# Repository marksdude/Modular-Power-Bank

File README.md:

# Modular-Power-Bank
A power bank with attachable modules
# Disclamer
None of the PCBs have been fully tested so I can't guarantee that they will function correctly.
# Features
- USB PD output up to 45W (may handle 60W)
- 0.91 inch OLED for status monitoring
- Attachable modules
- Repairable design
# Modules
- LED controller - Allows you to control 5V LEDs with Home Assistant

I also plan to make a LiPo charger module that will support charging up to 3S LiPos.

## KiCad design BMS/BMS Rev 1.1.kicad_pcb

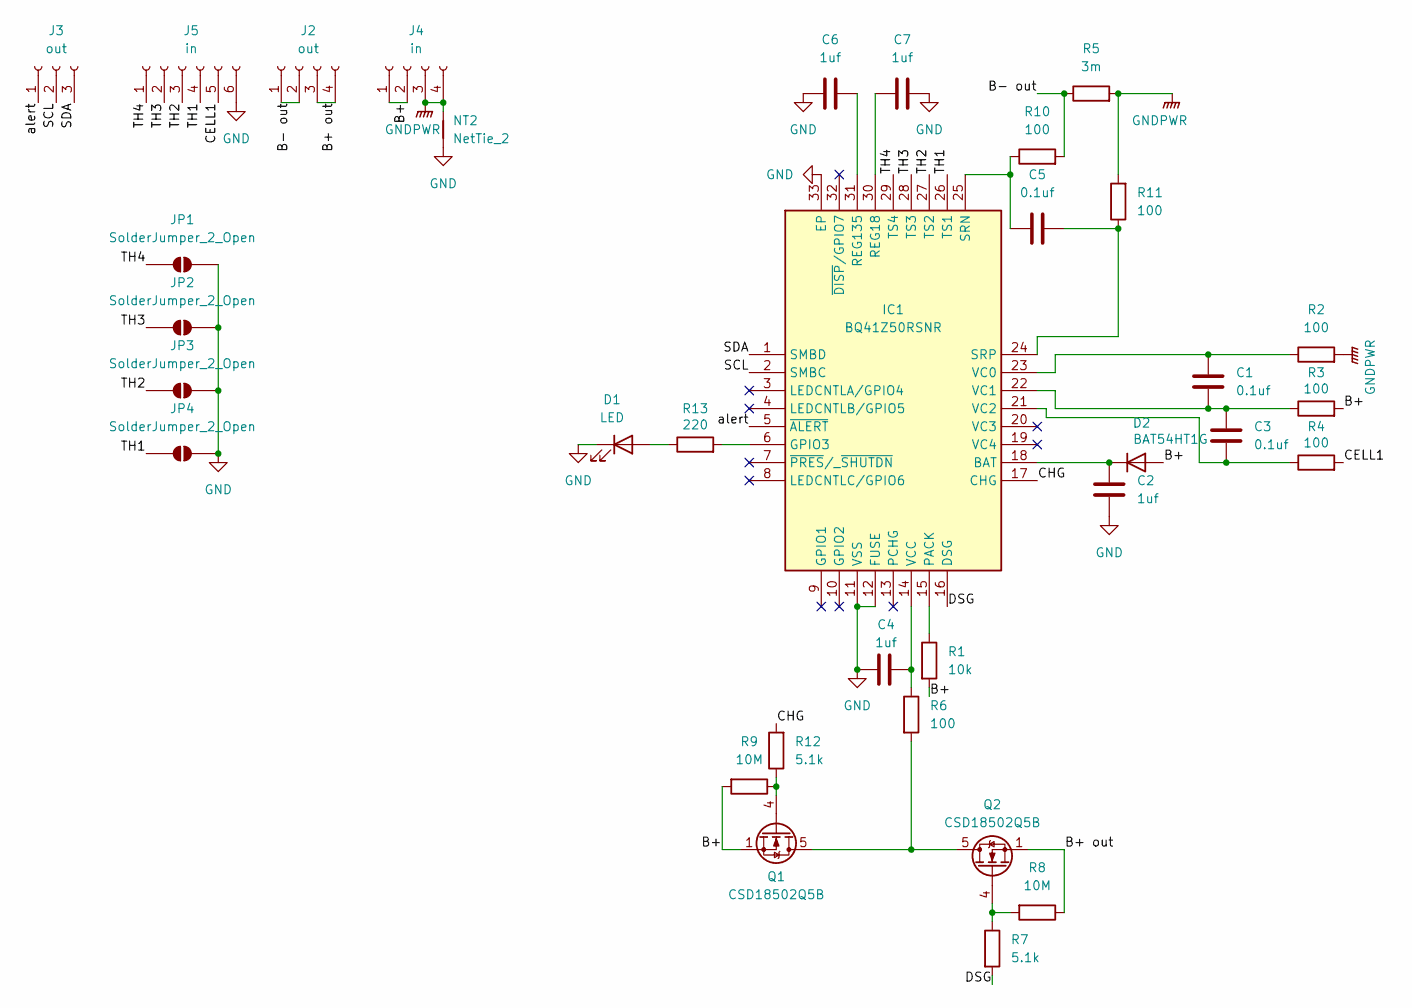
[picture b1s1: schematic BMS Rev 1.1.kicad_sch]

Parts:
C1, C3: 0.1uf; C_0402_1005Metric_Pad0.74x0.62mm_HandSolder
C2, C4, C6, C7: 1uf; C_0402_1005Metric_Pad0.74x0.62mm_HandSolder
C5: 0.1uf; C_0201_0603Metric_Pad0.64x0.40mm_HandSolder
D1: LED; LED_0402_1005Metric_Pad0.77x0.64mm_HandSolder
D2: BAT54HT1G; D_SOD-323_HandSoldering
IC1: BQ41Z50RSNR; QFN40P400X400X80-33N-D; Manufacturer_Part_Number BQ41Z50RSNR
J2: out; JST_VH_S4P-VH_1x04_P3.96mm_Horizontal
J3: out; JST_ZH_B3B-ZR_1x03_P1.50mm_Vertical
J4: in; JST_VH_S4P-VH_1x04_P3.96mm_Horizontal
J5: in; JST_ZH_B6B-ZR_1x06_P1.50mm_Vertical
JP1, JP2, JP3, JP4: SolderJumper_2_Open; SolderJumper-2_P1.3mm_Open_RoundedPad1.0x1.5mm
NT2: NetTie_2; NetTie-2_SMD_Pad0.5mm
Q1, Q2: CSD18502Q5B; TDSON-8-1
R1: 10k; R_0603_1608Metric_Pad0.98x0.95mm_HandSolder
R2, R3, R4, R10, R11: 100; R_0402_1005Metric_Pad0.72x0.64mm_HandSolder
R5: 3m; R_2512_6332Metric_Pad1.40x3.35mm_HandSolder
R6: 100; R_0603_1608Metric_Pad0.98x0.95mm_HandSolder
R7, R12: 5.1k; R_0402_1005Metric_Pad0.72x0.64mm_HandSolder
R8, R9: 10M; R_0402_1005Metric_Pad0.72x0.64mm_HandSolder
R13: 220; R_0402_1005Metric_Pad0.72x0.64mm_HandSolder

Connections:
/B+: D2.2 (A), J4.1, J4.2, Q1.1 (S), Q1.2 (S), Q1.3 (S), R1.2, R3.2, R9.2
/B+ out: J2.3, J2.4, Q2.1 (S), Q2.2 (S), Q2.3 (S), R8.1
/B- out: J2.1, J2.2, R5.1, R10.2
/CELL1: J5.5, R4.2
/CHG: IC1.17 (CHG), R12.2; also elsewhere on the board
/DSG: IC1.16 (DSG), R7.2; also elsewhere on the board
/SCL: IC1.2 (SMBC), J3.2; also elsewhere on the board
/SDA: IC1.1 (SMBD), J3.3; also elsewhere on the board
/TH1: IC1.26 (TS1), J5.4, JP4.1 (A); also elsewhere on the board
/TH2: IC1.27 (TS2), J5.3, JP3.1 (A); also elsewhere on the board
/TH3: IC1.28 (TS3), J5.2, JP2.1 (A); also elsewhere on the board
/TH4: IC1.29 (TS4), J5.1, JP1.1 (A); also elsewhere on the board
/alert: IC1.5 (~ALERT), J3.1; also elsewhere on the board
GND: C2.2, C4.1, C6.1, C7.2, D1.1 (K), IC1.11 (VSS), IC1.12 (FUSE), IC1.33 (EP), J5.6, JP1.2 (B), JP2.2 (B), JP3.2 (B), JP4.2 (B), NT2.1; also elsewhere on the board
GNDPWR: J4.3, J4.4, NT2.2, R2.2, R5.2, R11.2
unnamed: D1.2 (A), R13.1
unnamed 16: C2.1, D2.1 (K), IC1.18 (BAT); also elsewhere on the board
unnamed 17: IC1.6 (GPIO3), R13.2; also elsewhere on the board
unnamed 18: IC1.15 (PACK), R1.1; also elsewhere on the board
unnamed 19: C7.1, IC1.30 (REG18); also elsewhere on the board
unnamed 20: C6.2, IC1.31 (REG135); also elsewhere on the board
unnamed 21: C5.1, IC1.25 (SRN), R10.1; also elsewhere on the board
unnamed 22: C5.2, IC1.24 (SRP), R11.1; also elsewhere on the board
unnamed 23: C1.1, IC1.23 (VC0), R2.1; also elsewhere on the board
unnamed 24: C1.2, C3.1, IC1.22 (VC1), R3.1; also elsewhere on the board
unnamed 25: C3.2, IC1.21 (VC2), R4.1; also elsewhere on the board
unnamed 26: C4.2, IC1.14 (VCC), R6.1; also elsewhere on the board
unnamed: Q1.5 (D), Q2.5 (D), R6.2
unnamed: Q1.4 (G), R9.1, R12.1
unnamed: Q2.4 (G), R7.1, R8.2

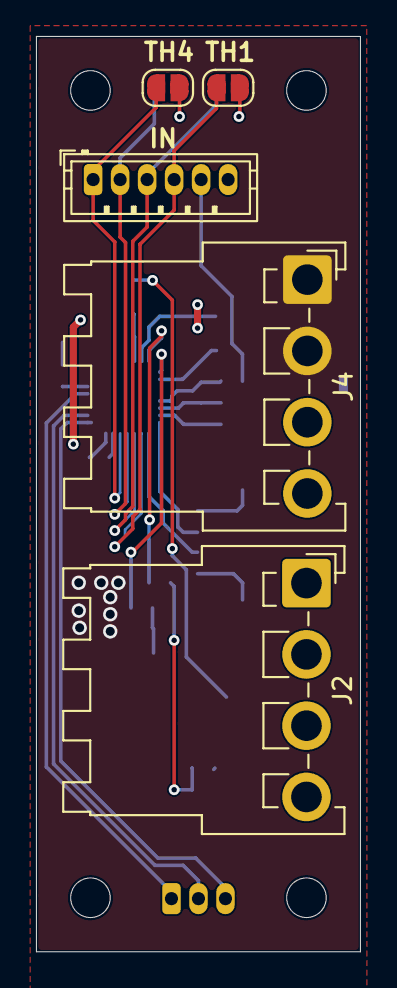
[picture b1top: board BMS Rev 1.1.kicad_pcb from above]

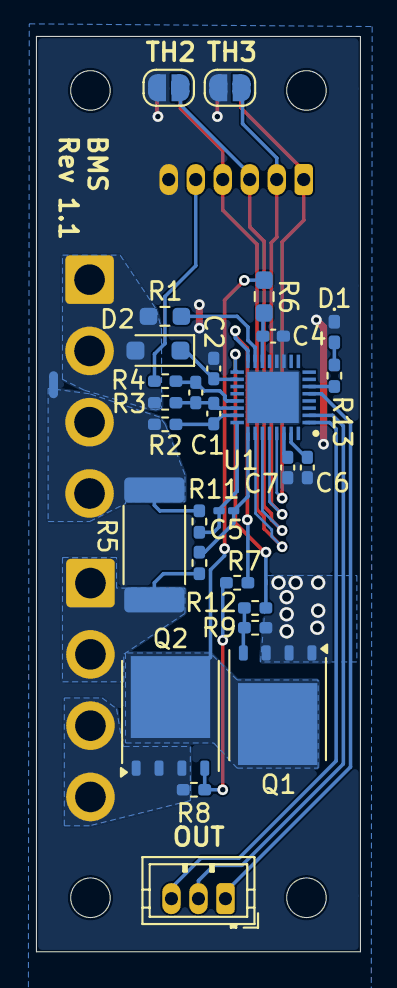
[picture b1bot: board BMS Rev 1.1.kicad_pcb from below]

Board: 2 copper layers, 18.0 x 50.8 mm, 34 parts (29 on the bottom side), 30 nets.

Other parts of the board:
U1: BQ41Z50RSNR; QFN40P400X400X80-33N-D

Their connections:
/CHG: U1.17 (CHG); also elsewhere on the board
/DSG: U1.16 (DSG); also elsewhere on the board
/SCL: U1.2 (SMBC); also elsewhere on the board
/SDA: U1.1 (SMBD); also elsewhere on the board
/TH1: U1.26 (TS1); also elsewhere on the board
/TH2: U1.27 (TS2); also elsewhere on the board
/TH3: U1.28 (TS3); also elsewhere on the board
/TH4: U1.29 (TS4); also elsewhere on the board
/alert: U1.5 (~ALERT); also elsewhere on the board
GND: U1.11 (VSS), U1.12 (FUSE), U1.33 (EP); also elsewhere on the board
unnamed 16: U1.18 (BAT); also elsewhere on the board
unnamed 17: U1.6 (GPIO3); also elsewhere on the board
unnamed 18: U1.15 (PACK); also elsewhere on the board
unnamed 19: U1.30 (REG18); also elsewhere on the board
unnamed 20: U1.31 (REG135); also elsewhere on the board
unnamed 21: U1.25 (SRN); also elsewhere on the board
unnamed 22: U1.24 (SRP); also elsewhere on the board
unnamed 23: U1.23 (VC0); also elsewhere on the board
unnamed 24: U1.22 (VC1); also elsewhere on the board
unnamed 25: U1.21 (VC2); also elsewhere on the board
unnamed 26: U1.14 (VCC); also elsewhere on the board

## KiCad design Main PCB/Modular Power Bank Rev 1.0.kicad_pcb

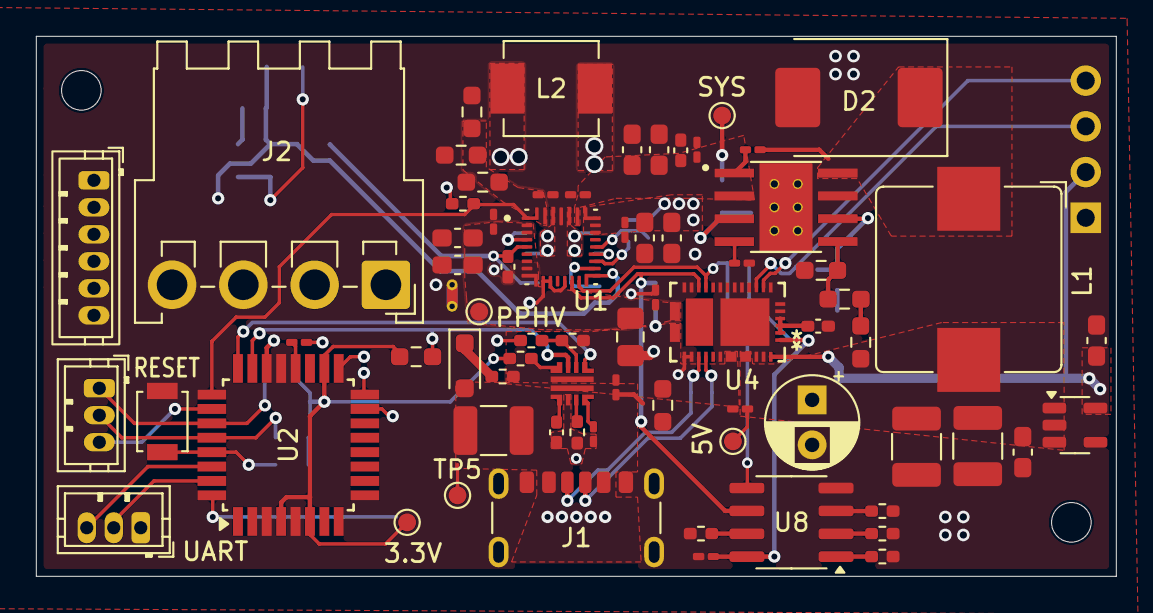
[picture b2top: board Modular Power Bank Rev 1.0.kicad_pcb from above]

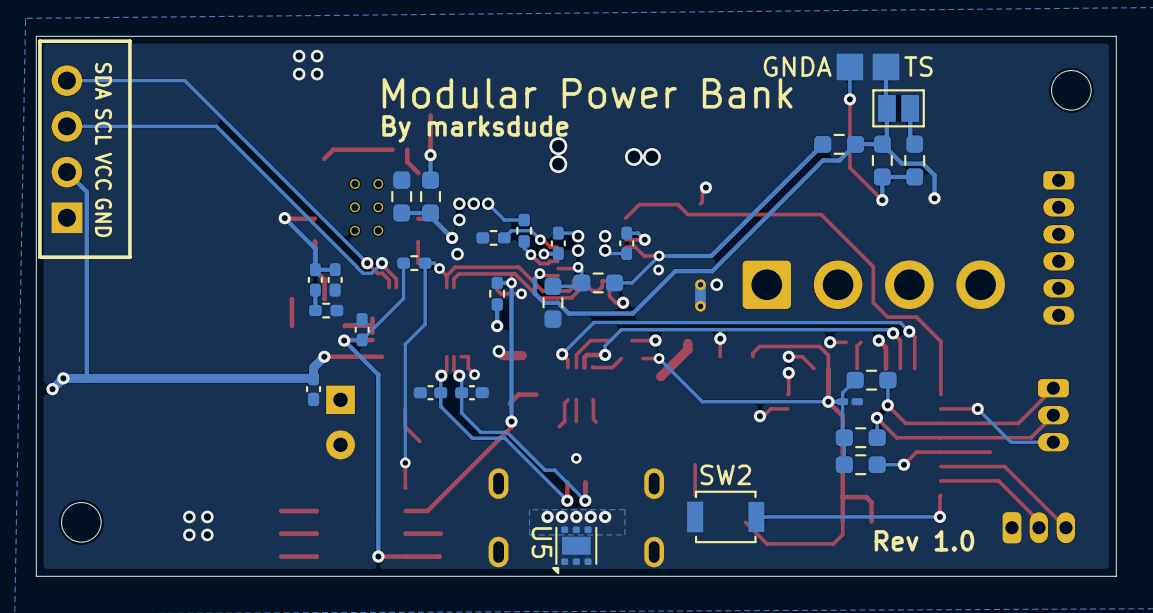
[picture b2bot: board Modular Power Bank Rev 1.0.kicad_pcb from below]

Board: 4 copper layers, 60.0 x 30.0 mm, 100 parts (29 on the bottom side), 58 nets.

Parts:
C1, C13, C14, C16, C21, C25, C33, C41, C46, C48: 0.1uf; C_0201_0603Metric_Pad0.64x0.40mm_HandSolder
C3, C4: 330pf; C_0402_1005Metric_Pad0.74x0.62mm_HandSolder
C5, C8, C43: 10nf; C_0201_0603Metric_Pad0.64x0.40mm_HandSolder
C6, C20: 4.7uf; C_0402_1005Metric_Pad0.74x0.62mm_HandSolder
C9: 2.2nf; C_0402_1005Metric_Pad0.74x0.62mm_HandSolder
C10, C11, C12, C22, C24, C26, C29, C35: 10uf; C_0603_1608Metric_Pad1.08x0.95mm_HandSolder
C15, C36, C37: 10uf; C_0402_1005Metric_Pad0.74x0.62mm_HandSolder
C17, C18, C19, C42: 10uf; R_0603_1608Metric_Pad0.98x0.95mm_HandSolder
C31, C32: 0.047uf; C_0402_1005Metric_Pad0.74x0.62mm_HandSolder
C39: 22uf; C_0805_2012Metric_Pad1.18x1.45mm_HandSolder
C40: 0,1uf; C_0201_0603Metric_Pad0.64x0.40mm_HandSolder
C44: 1100pf; C_0402_1005Metric_Pad0.74x0.62mm_HandSolder
C45, C50, C51: 47uf; C_1210_3225Metric_Pad1.33x2.70mm_HandSolder
C47: 22pf; C_0402_1005Metric_Pad0.74x0.62mm_HandSolder
C49: 100uf; CP_Radial_D5.0mm_P2.50mm
D1: D; D_SOD-323_HandSoldering
D2: D; D_SMC
J1: USB_C_Receptacle_PowerOnly_6P; USB_C_Receptacle_GCT_USB4125-xx-x-0190_6P_TopMnt_Horizontal
J2: bat; JST_VH_S4P-VH_1x04_P3.96mm_Horizontal
J3: Conn_01x03_Pin; JST_ZH_B3B-ZR_1x03_P1.50mm_Vertical
J4: i2c; JST_ZH_B3B-ZR_1x03_P1.50mm_Vertical
J6: program; JST_ZH_B6B-ZR_1x06_P1.50mm_Vertical
JP1: SolderJumper_2_Open; SolderJumper-2_P1.3mm_Open_Pad1.0x1.5mm
L1: 4.7uh; L_Bourns_SRP1038C_10.0x10.0mm
L2: 1uH; L_Vishay_IHLP-2020
NT1: NetTie_2; NetTie-2_THT_Pad0.3mm
R1, R2: 4.7k; R_0603_1608Metric_Pad0.98x0.95mm_HandSolder
R3, R18, R32: 10k; R_0603_1608Metric_Pad0.98x0.95mm_HandSolder
R4, R5, R6, R8, R10, R11: 10k; R_0402_1005Metric_Pad0.72x0.64mm_HandSolder
R7: 470k; R_0402_1005Metric_Pad0.72x0.64mm_HandSolder
R12: 3k 1-2%; R_0402_1005Metric_Pad0.72x0.64mm_HandSolder
R13: 100k; R_0603_1608Metric_Pad0.98x0.95mm_HandSolder
R14: 137k; R_0603_1608Metric_Pad0.98x0.95mm_HandSolder
R15: 100; R_0402_1005Metric_Pad0.72x0.64mm_HandSolder
R16: 5.23k; R_0603_1608Metric_Pad0.98x0.95mm_HandSolder
R17: 30.1k; R_0603_1608Metric_Pad0.98x0.95mm_HandSolder
R19, R20: 4.7k; R_0402_1005Metric_Pad0.72x0.64mm_HandSolder
R21: 10.2k; R_0603_1608Metric_Pad0.98x0.95mm_HandSolder
R22: 27k; R_0402_1005Metric_Pad0.72x0.64mm_HandSolder
R25: 1k; R_0402_1005Metric_Pad0.72x0.64mm_HandSolder
R26: 10; R_0402_1005Metric_Pad0.72x0.64mm_HandSolder
R27: 665k; R_0603_1608Metric_Pad0.98x0.95mm_HandSolder
R28: 130k; R_0603_1608Metric_Pad0.98x0.95mm_HandSolder
R29: 37.4k; R_0402_1005Metric_Pad0.72x0.64mm_HandSolder
R30: 51.1; R_0603_1608Metric_Pad0.98x0.95mm_HandSolder
R31: 1.96k; R_0603_1608Metric_Pad0.98x0.95mm_HandSolder
SW1, SW2: SW_Push; SW_SPST_B3U-1000P
TH1: Thermistor_NTC; ntc
TP1: SYS; TestPoint_Pad_D1.0mm
TP2: 5V; TestPoint_Pad_D1.0mm
TP3: 3.3V; TestPoint_Pad_D1.0mm
TP4: PPHV; TestPoint_Pad_D1.0mm
TP5: USB PD OUT; TestPoint_Pad_D1.0mm
U1: BQ25792RQMR; QFN40P400X400X100-29N
U2: ATmega328P-A; TQFP-32_7x7mm_P0.8mm
U3: OLED 0.91 inch; SSD1306-0.91-OLED-4pin-128x32
U4: PTPS25751DREFR; WQFN38_REF_TEX
U5: TVS2200DRV; WSON-6-1EP_2x2mm_P0.65mm_EP1x1.6mm
U6: TPS54531DDAR; CONV_TPS54531DDAR
U7: TLV75533PDBV; SOT-23-5
U8: CAT24C256; SOIC-8_3.9x4.9mm_P1.27mm
U9: TPS259461LRPWR; VQFN10_RPW_TEX

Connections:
+3V3: C1.2, C10.1, C15.1, R1.1, R2.1, R3.2, R4.1, R8.1, R32.2, TP3.1 (1_1), U2.4 (VCC), U2.6 (VCC), U2.18 (AVCC), U3.2 (VCC), U4.38 (VIN_3V3), U7.5 (OUT)
+BATT: C21.1, C22.1, C24.1, J2.1, J2.2, R15.2, U1.22 (BAT), U1.23 (BAT), U1.24 (SDRV)
-BATT: C1.1, C3.2, C4.1, C5.2, C6.2, C8.2, C10.2, C11.1, C12.1, C13.1, C14.2, C15.2, C16.2, C17.2, C18.2, C19.2, C20.1, C21.2, C22.2, C24.2, C25.2, C26.2, C29.2, C35.2, C36.2, C37.2, C39.2, C40.2, C41.2, C42.2, C45.2, C46.2, C47.2, C49.2, C50.2, C51.2, D2.2 (A), J1.A12 (GND), J1.B12 (GND), J1.S1 (SHIELD), J2.3, J2.4, J3.1, J6.6, NT1.1, R5.1, R6.1, R10.1, R11.1, R12.1, R13.2, R28.2, R29.2, R31.2, SW1.2, SW2.2, U1.27 (GND), U2.3 (GND), U2.5 (GND), U2.21 (GND), U3.1 (GND), U4.5 (GPIO0), U4.6 (GPIO1), U4.7 (GPIO2), U4.10 (*I2CT_IRQ), U4.11 (GND), U4.12 (GND), U4.13 (GPIO11), U4.14 (GND), U4.18 (*I2CC_IRQ), U4.19 (GPIO3), U4.26 (GPIO4/USB_P/LD1), U4.27 (GPIO5/USB_N/LD2), U4.31 (GND), U4.36 (GPIO7), U4.37 (GPIO6), U4.39 (GND), U5.1 (GND), U5.2 (GND), U5.3 (GND), U5.7 (GND), U6.7 (GND), U6.9 (POWERPAD), U7.2 (GND), U8.4 (GND)
/BATP: R15.1, U1.18 (BATP)
/BTST1: C31.1, U1.4 (BTST1)
/BTST2: C32.2, U1.19 (BTST2)
/CC1: C4.2, J1.A5 (CC1), U4.28 (CC1)
/CC2: C3.1, J1.B5 (CC2), U4.29 (CC2)
/COMP: C9.1, C47.1, U6.6 (COMP)
/DVDT: C44.1, U9.7 (DVDT)
/EN 5V: R27.2, R28.1, U6.3 (EN)
/I2CC_SCL: J6.1, R19.2, U1.14 (SCL), U4.17 (I2CC_SCL), U8.6 (SCL)
/I2CC_SDA: J6.2, R20.2, U1.15 (SDA), U4.16 (I2CC_SDA), U8.5 (SDA)
/ILIM_HIZ: R13.1, R14.1, U1.17 (ILIM_HIZ)
/LDO_3V3: C14.1, C36.1, R19.1, R20.1, U4.1 (LDO_3V3), U8.8 (VCC)
/MISO: J6.4, U2.16 (PB4)
/MOSI: J6.5, U2.15 (PB3)
/OUT: C45.1, D1.2 (A), J1.A9 (VBUS), J1.B9 (VBUS), TP5.1 (1_1), U5.4 (IN), U5.5 (IN), U5.6 (IN), U9.6 (OUT)
/OVLO: R7.1, R22.1, U9.2 (OVLO)
/PG efuse: R32.1, U2.23 (PC0), U9.3 (PG/SPLYGD)
/PP5V: C35.1, C41.1, C49.1, C50.1, C51.1, L1.2, R30.1, TP2.1 (1_1), U4.34 (PP5V), U4.35 (PP5V), U7.1 (IN), U7.3 (EN)
/REGN: C20.2, R14.2, R16.1, U1.5 (REGN)
/RXD: J3.3, U2.30 (PD0)
/SCK: J6.3, U2.17 (PB5)
/SCL: J4.2, R1.2, U2.28 (PC5), U3.3 (SCL), U4.9 (I2CT_SCL)
/SDA: J4.1, R2.2, U2.27 (PC4), U3.4 (SDA), U4.8 (I2CT_SDA)
/SS: C8.1, U6.4 (SS)
/SW1: C31.2, L2.1, U1.28 (SW1)
/SW2: C32.1, L2.2, U1.26 (SW2)
/SYS: C5.1, C6.1, C25.1, C26.1, C29.1, R27.1, TP1.1 (1_1), U1.25 (SYS), U6.2 (VIN)
/TS: JP1.1 (A), R16.2, R17.1, TH1.1, U1.16 (TS), U2.22 (ADC7)
/TXD: J3.2, U2.31 (PD1)
/VSENSE: R21.2, R31.1, U6.5 (VSENSE)
/alert: J4.3, U2.26 (PC3)
/efuse EN: U2.24 (PC1), U9.1 (EN/UVLO)
/efuse IN: C42.1, C46.1, R7.2, R26.1, U4.23 (VBUS_IN), U4.24 (VBUS_IN), U4.25 (VBUS_IN), U4.32 (VBUS), U4.33 (VBUS), U9.5 (IN)
/nupp: SW2.1, U2.32 (PD2)
/pgth: R8.2, U9.4 (PGTH/FLT)
/reset: R3.1, SW1.1, U2.29 (~RESET/PC6)
/stat: R4.2, U1.1 (STAT), U2.25 (PC2)
GNDA: C33.2, C43.1, C44.2, NT1.2, R17.2, R18.2, R22.2, R25.2, TH1.2, U1.10 (ACDRV2), U1.11 (ACDRV1), U1.13 (~CE), U9.8 (GND)
unnamed: C9.2, R29.1
unnamed: D1.1 (K), R26.2
unnamed: C48.2, D2.1 (K), L1.1, U6.8 (PH)
unnamed: JP1.2 (B), R18.1
unnamed: R21.1, R30.2
unnamed: C16.1, C17.1, C18.1, C19.1, U1.29 (PMID)
unnamed: R12.2, U1.20 (PROG)
unnamed: C33.1, U2.20 (AREF)
unnamed: C37.1, U4.2 (ADCIN1), U4.3 (ADCIN2), U4.4 (LDO_1V5)
unnamed: C48.1, U6.1 (BOOT)
unnamed: R10.2, U8.1 (A0)
unnamed: R6.2, U8.2 (A1)
unnamed: R5.2, U8.3 (A2)
unnamed: R11.2, U8.7 (WP)
unnamed: R25.1, U9.9 (ILM)
unnamed: C43.2, U9.10 (ITIMER)
VBUS: C11.2, C12.2, C13.2, C39.1, C40.1, TP4.1 (1_1), U1.2 (VBUS), U1.3 (VBUS), U1.8 (VAC2), U1.9 (VAC1), U4.20 (PPHV), U4.21 (PPHV), U4.22 (PPHV)

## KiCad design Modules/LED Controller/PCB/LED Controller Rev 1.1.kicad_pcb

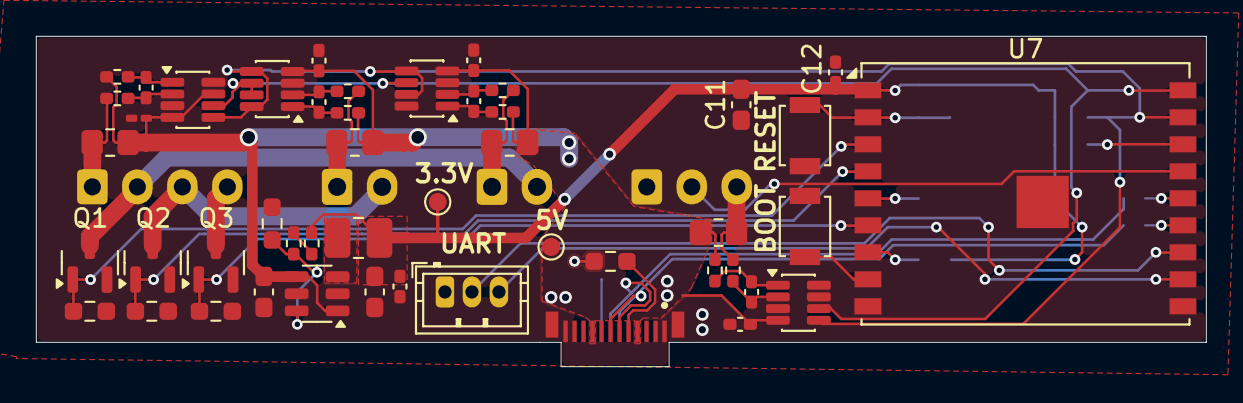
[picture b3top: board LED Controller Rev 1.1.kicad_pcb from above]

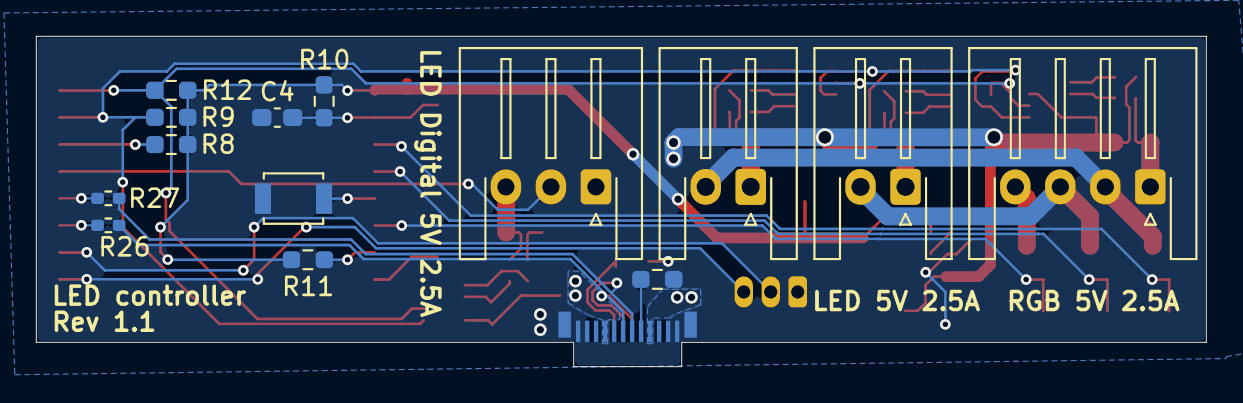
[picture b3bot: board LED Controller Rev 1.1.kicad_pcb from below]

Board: 2 copper layers, 65.0 x 18.4 mm, 62 parts (14 on the bottom side), 40 nets.

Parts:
C1: 4.7uf; C_0603_1608Metric_Pad1.08x0.95mm_HandSolder
C2: 22uf; C_0603_1608Metric_Pad1.08x0.95mm_HandSolder
C3: 120pf; C_0402_1005Metric_Pad0.74x0.62mm_HandSolder
C4: 1uf; C_0603_1608Metric_Pad1.08x0.95mm_HandSolder
C5, C6, C7, C9, C10, C12, C13, C14: 100nF; C_0402_1005Metric_Pad0.74x0.62mm_HandSolder
C8: 100nF; C_0201_0603Metric_Pad0.64x0.40mm_HandSolder
C11: 22uF; C_0603_1608Metric_Pad1.08x0.95mm_HandSolder
J1, J2: LED; JST_XH_S2B-XH-A-1_1x02_P2.50mm_Horizontal
J3: UP32-1-C-H-G-BMT-P24; SAMESKY_UP32-1-C-H-G-BMT-P24
J4: RGB 2A max; JST_XH_S4B-XH-A-1_1x04_P2.50mm_Horizontal
J5: RGB 2A max; JST_XH_S3B-XH-A-1_1x03_P2.50mm_Horizontal
J7: UART; JST_ZH_B3B-ZR_1x03_P1.50mm_Vertical
L1: 1uH; L_1008_2520Metric_Pad1.43x2.20mm_HandSolder
Q1, Q2, Q3: AO3400A; SOT-23
R1: 300k; R_0402_1005Metric_Pad0.72x0.64mm_HandSolder
R2, R6, R7, R8, R10, R11: 10k; R_0603_1608Metric_Pad0.98x0.95mm_HandSolder
R3: 100k; R_0603_1608Metric_Pad0.98x0.95mm_HandSolder
R4, R5: 5.1k; R_0603_1608Metric_Pad0.98x0.95mm_HandSolder
R9, R12: 4.7k; R_0603_1608Metric_Pad0.98x0.95mm_HandSolder
R13, R14, R17, R18, R20, R21, R23, R24: 10; R_0402_1005Metric_Pad0.72x0.64mm_HandSolder
R15, R16, R19, R22: 20m; R_0805_2012Metric_Pad1.20x1.40mm_HandSolder
R25: 150k; R_0402_1005Metric_Pad0.72x0.64mm_HandSolder
R26, R27: 22; R_0402_1005Metric_Pad0.72x0.64mm_HandSolder
SW1: ON/OFF; SW_SPST_B3U-1000P
SW2: RESET; SW_SPST_B3U-1000P
SW3: BOOT; SW_SPST_B3U-1000P
TP1: 3.3V; TestPoint_Pad_D1.0mm
TP2: 5V; TestPoint_Pad_D1.0mm
U1, U2, U3, U5: INA219AxDCN; SOT-23-8
U4: TPS62A02APDDC; SOT-23-6
U7: ESP32-C3-WROOM-02; ESP32-C3-WROOM-02U

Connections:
+3.3V: C2.1, C3.1, C11.2, C12.2, L1.2, R8.1, R9.2, R10.1, R11.2, R12.2, R25.2, TP1.1 (1_1), U7.1 (3V3)
/B: J4.4, Q3.3 (D)
/D+: J3.A6 (DP1), J3.B6 (DP2), R27.1
/D-: J3.A7 (DN1), J3.B7 (DN2), R26.1
/FB: R1.1, R3.2, U4.6 (FB)
/G: J1.2, J4.2, Q1.3 (D)
/IO8: R11.1, U7.7 (IO8)
/LED1: Q3.1 (G), R7.1, U7.6 (IO7)
/LED1 out: J2.1, R19.1, R21.1
/LED2: Q2.1 (G), R6.1, U7.4 (IO5)
/LED2 out: J1.1, R22.1, R24.1
/LED3: Q1.1 (G), R2.1, U7.3 (IO4)
/LED4: J5.2, U7.15 (IO3)
/R: J2.2, J4.3, Q2.3 (D)
/RGB: J4.1, R16.1, R18.1
/RGB digital: J5.3, R14.1, R15.1
/RXD: J7.3, U7.11 (IO20/RXD)
/SCL: R9.1, U1.5 (SCL), U2.5 (SCL), U3.5 (SCL), U3.8 (A1), U5.5 (SCL), U5.7 (A0), U7.17 (IO1)
/SDA: R12.1, U1.6 (SDA), U2.6 (SDA), U3.6 (SDA), U3.7 (A0), U5.6 (SDA), U7.18 (IO0)
/TXD: J7.2, U7.12 (IO21/TXD)
/boot: SW3.2, U7.8 (IO9)
GND: C1.2, C2.2, C3.2, C4.1, C5.1, C8.1, C10.1, C11.1, C12.1, C14.1, J3.A1 (GND), J3.A12 (GND__1), J3.B1 (GND__2), J3.B12 (GND__3), J3.SH1 (SHIELD), J3.SH2 (SHIELD__1), J3.SH3 (SHIELD__2), J3.SH4 (SHIELD__3), J5.1, J7.1, Q1.2 (S), Q2.2 (S), Q3.2 (S), R2.2, R3.1, R4.1, R5.1, R6.2, R7.2, SW1.1, SW2.1, SW3.1, U1.3 (GND), U1.7 (A0), U1.8 (A1), U2.3 (GND), U2.8 (A1), U3.3 (GND), U4.2 (GND), U4.5 (PG), U5.3 (GND), U5.8 (A1), U7.9 (GND), U7.19 (GND)
unnamed: J3.A5 (CC1), R4.2
unnamed: J3.B5 (CC2), R5.2
unnamed: R1.2, R25.1
unnamed: C6.1, R13.2, U1.1 (IN+)
unnamed: C6.2, R14.2, U1.2 (IN-)
unnamed: C7.1, R17.2, U2.1 (IN+)
unnamed: C7.2, R18.2, U2.2 (IN-)
unnamed: C9.1, R20.2, U3.1 (IN+)
unnamed: C9.2, R21.2, U3.2 (IN-)
unnamed: L1.1, U4.3 (SW)
unnamed: C13.1, R23.2, U5.1 (IN+)
unnamed: C13.2, R24.2, U5.2 (IN-)
unnamed: C4.2, R10.2, SW2.2, U7.2 (EN)
unnamed: R8.2, U7.16 (IO2)
unnamed: SW1.2, U7.5 (IO6)
unnamed: R26.2, U7.13 (IO18)
unnamed: R27.2, U7.14 (IO19)
VBUS: C1.1, C5.2, C8.2, C10.2, C14.2, J3.A4 (VBUS), J3.A9 (VBUS__1), J3.B4 (VBUS__2), J3.B9 (VBUS__3), R13.1, R15.2, R16.2, R17.1, R19.2, R20.1, R22.2, R23.1, TP2.1 (1_1), U1.4 (VS), U2.4 (VS), U2.7 (A0), U3.4 (VS), U4.1 (EN), U4.4 (VIN), U5.4 (VS)
